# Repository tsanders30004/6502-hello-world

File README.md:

# 6502 'HELLO WORLD 6502' PCB

## INTRODUCTION
- The repo has all of the files necessary to build Ben Eater's HELLO WORLD 8-bit computer on a PCB.
- When I started my 6502 learning journey two years ago, it was so I could learn more about 6502 assembly language.
- I had little interest in hardware at the time.
- While I was doing my research, I stumbled on Ben Eater's '8-bit computer on a breadboard' YouTube series and decided to build my own computer.
- I quickly grew frustrated with breadboards so I decided to build a PCB instead.
- After many YouTube vidoes and a failed prototype, I was able to get a working PCB.
- The files in this repo are the result.

## EDA SOFTWARE
The schematics and PCB were designed with KiCad version 6.

## SCHEMATICS
- KiCad and PDF schematics are included.

### Bus vs. Labels

- When I drew the schematics, I could not figure out how to draw a bus.
- Instead, I used lables for the address and data pins, and a few other things.

## INPUTS
### Power
+5 and GND are connected to the circuit via the header pins in the upper-right corner of the PCB.

The PWR LED will illuminate when the PCB has power.

### Clock
You will need an external clock.

The clock signal should be connected to the CLK input pin in the upper-right corner of the PCB.

The CLK LED will illuminate when the circuit has a clock signal.

## OUTPUTS 
### Address and Data Pins
Output pins for each of the data and address lines are arranged vertically along the right side of the PCB.

You can connect these pins to an Arduino, oscilloscope, logic analyzer, etc. if you wish.

Leave them unconnected if you don't want to use them.

### LED's
There are LED's for each of the address and data lines along the bottom.  The LED's will illuminate when a program is running.

## IRQB and RESETB
Note the IRQB and RESETB switches directly above the 65C02 socket. 

When I drew the schematic, I was not certain how to wire the IRQB and RESETB signals using a button.  So I decided to use a slider switch instead; that way, I could connect/disconnect these signals however I wanted.

###  Resetting the Circuit
IMPORTANT:  To reset the cicuit, do the following:

1. Put the IRQB and RESETB slider switches in the UP position.
1. Put the IRQB slider switch in the DOWN position.
1. Put the RESETB slider switch in the DOWN position.

## FILES
|Filename|Description|
|-|-|
|6502_hello_world.kicad_pro|KiCad Project File|
|6502_hello_world.kicad_sch|KiCad Schematic File|
|6502_hello_world.kicad_pcb|KiCad PCB File|
|gerber_files.zip|Gerber Files|
|hello.s|Hello World Source Code|
|hello.out|Hello World Binary File|
|pcb_3d_model.png|Screen Shot of 3D Model|
|schematic.pdf|Schematics|

## CLOSING COMMENTS
- I am a hobbyist.  This is my first attempt at designing a PCB.
- When I started this project, I knew the basics of digital hardware.  But I knew nothing about PCB design.
- I learned how to solder and how to use KiCad via YouTube videos.
- PBCWay used the included gerber files to build the PCB.  They are probably suitable for other PCB manufacturers.
- If not, you can export you own gerber files with KiCad.

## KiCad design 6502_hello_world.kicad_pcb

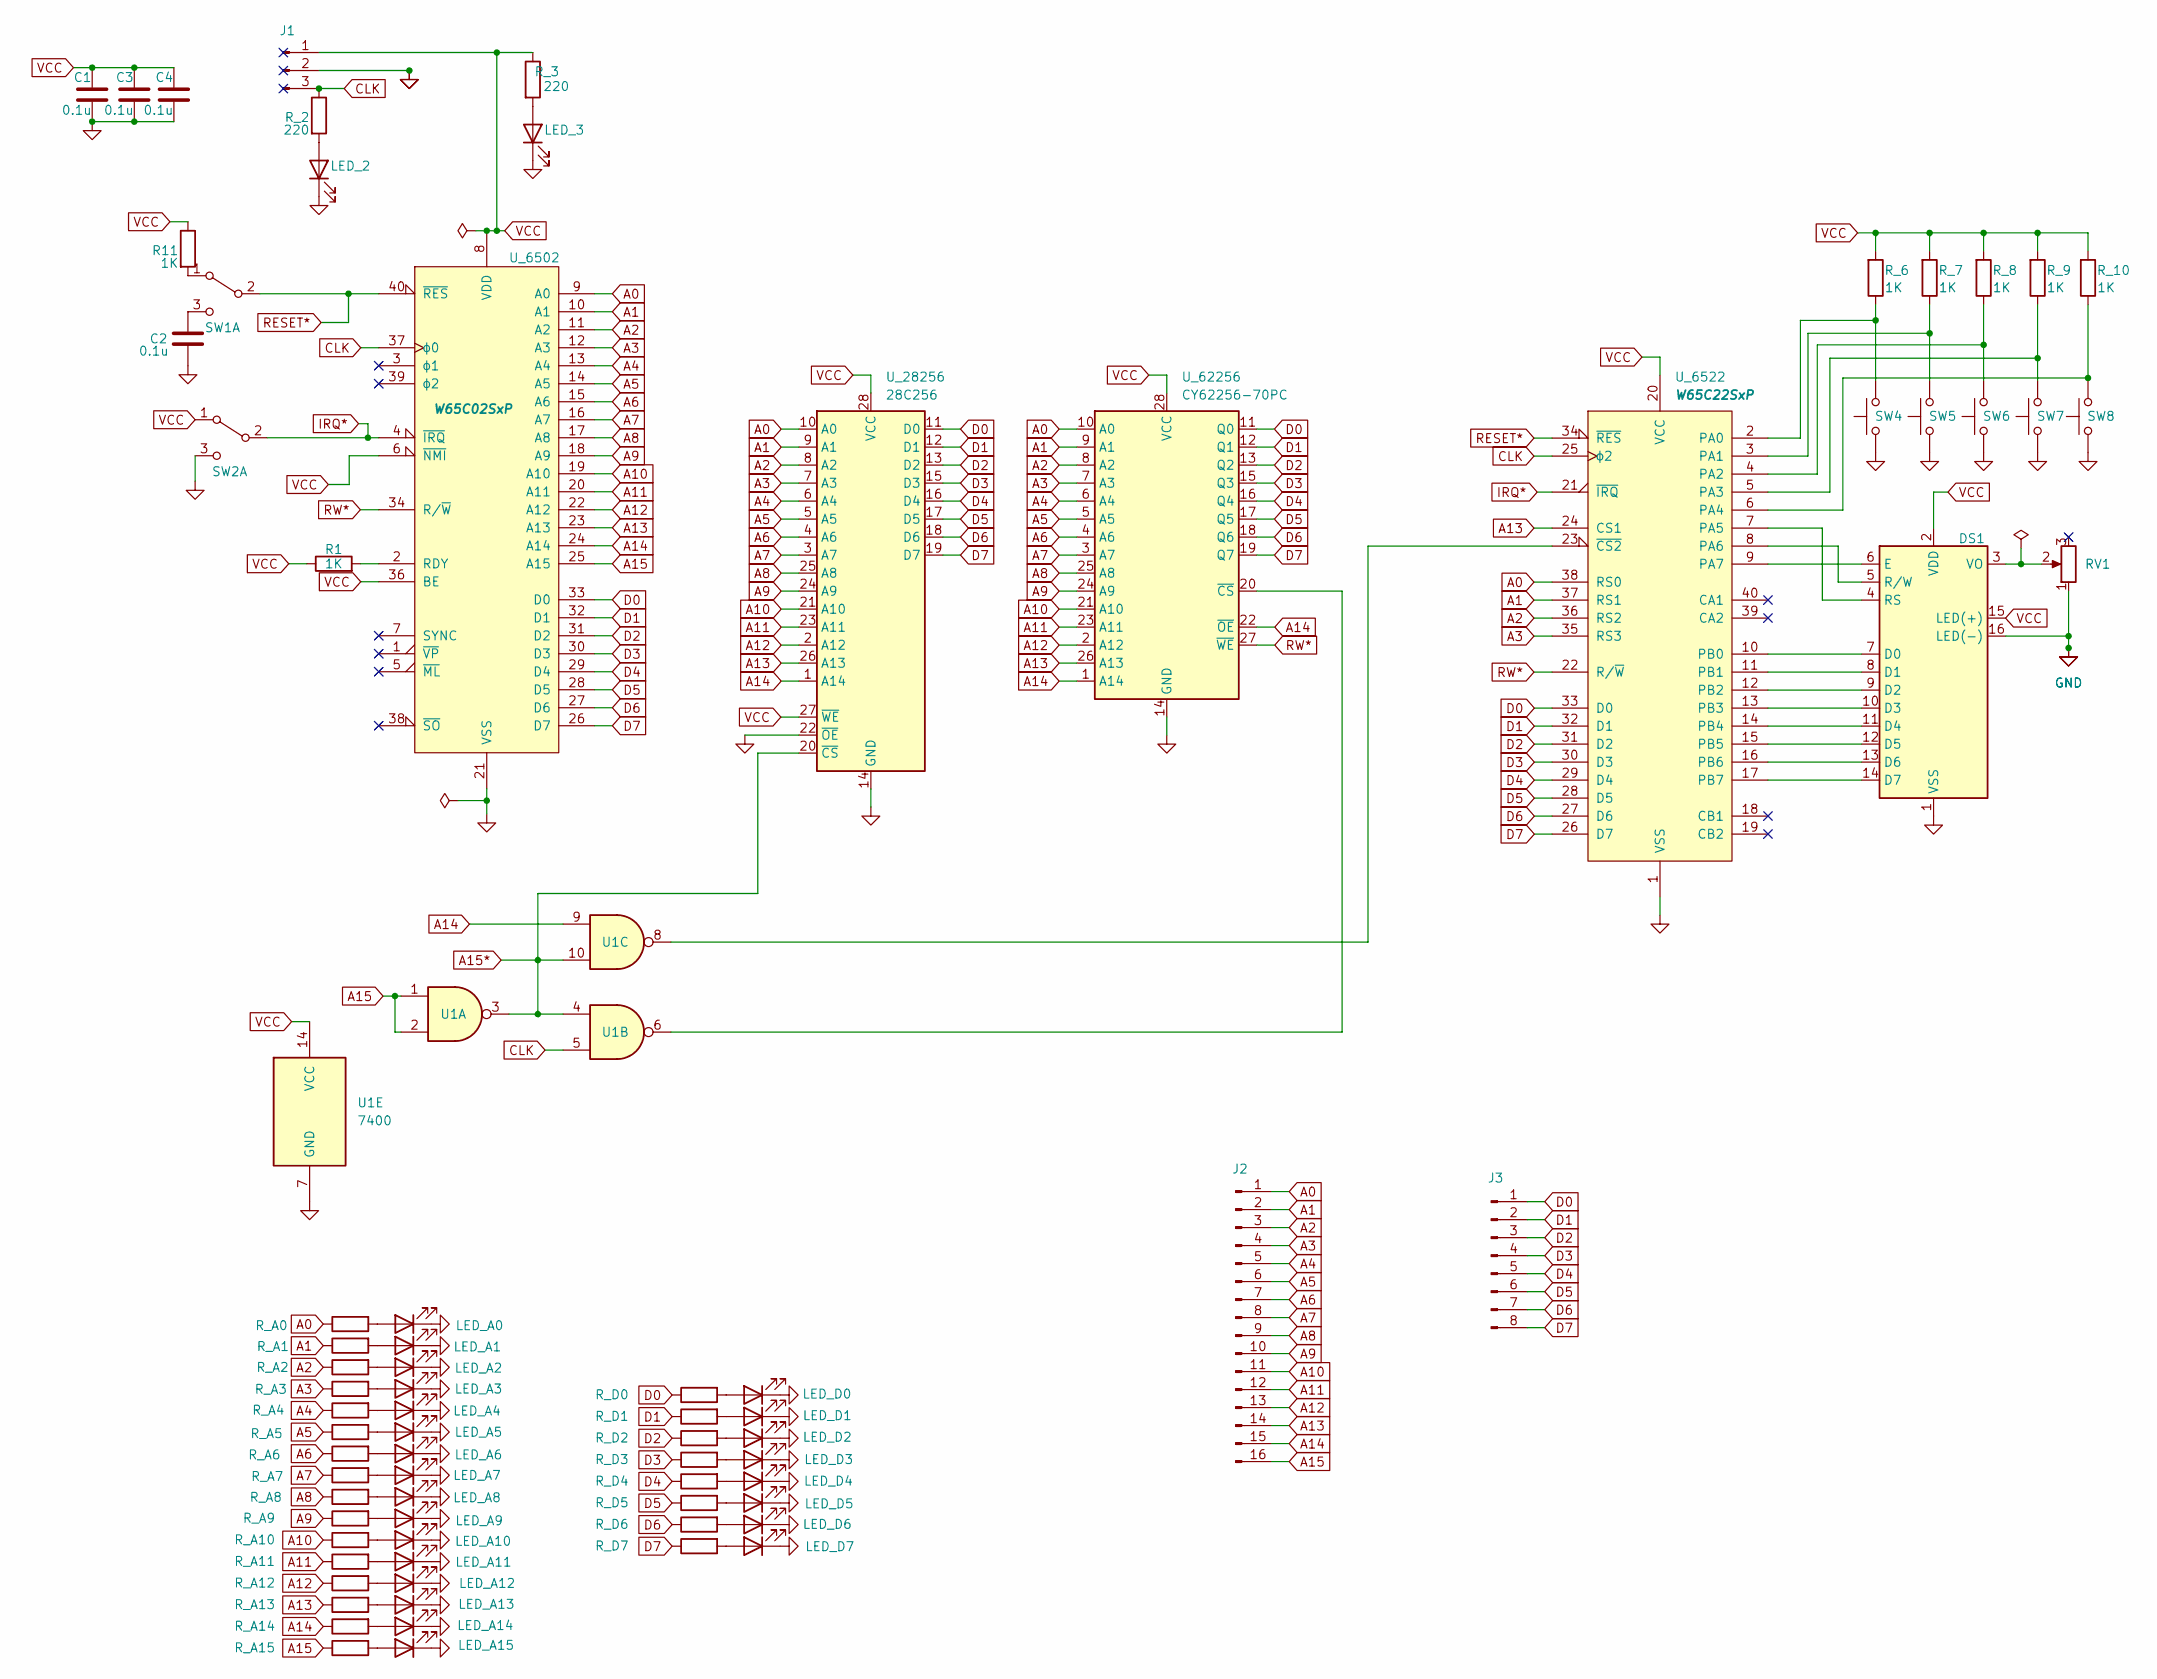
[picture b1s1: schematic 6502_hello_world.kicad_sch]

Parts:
C1, C2, C3, C4: 0.1u; C_Disc_D5.0mm_W2.5mm_P5.00mm
DS1: WC1602A
J1: Conn_01x03_Male; PinHeader_1x03_P2.54mm_Horizontal
J2: Conn_01x16_Male; PinHeader_1x16_P2.54mm_Horizontal
J3: Conn_01x08_Male; PinHeader_1x08_P2.54mm_Horizontal
LED_2, LED_3: LED; LED_D5.0mm
LED_A0, LED_A1, LED_A2, LED_A3, LED_A4, LED_A5, LED_A6, LED_A7, LED_A8, LED_A9, LED_A10, LED_A11, LED_A12, LED_A13, LED_A14, LED_A15: LED; LED_D5.0mm
LED_D0, LED_D1, LED_D2, LED_D3, LED_D4, LED_D5, LED_D6, LED_D7: LED; LED_D5.0mm
R1, R11: 1K; R_Axial_DIN0207_L6.3mm_D2.5mm_P10.16mm_Horizontal
RV1: R_Potentiometer; Potentiometer_Bourns_3266Y_Vertical
R_2, R_3: 220; R_Axial_DIN0207_L6.3mm_D2.5mm_P10.16mm_Horizontal
R_6, R_7, R_8, R_9, R_10: 1K; R_Axial_DIN0207_L6.3mm_D2.5mm_P10.16mm_Horizontal
R_A0, R_A1, R_A2, R_A3, R_A4, R_A5, R_A6, R_A7, R_A8, R_A9, R_A10, R_A11, R_A12, R_A13, R_A14, R_A15: 220; R_Axial_DIN0207_L6.3mm_D2.5mm_P10.16mm_Horizontal
R_D0, R_D1, R_D2, R_D3, R_D4, R_D5, R_D6, R_D7: 220; R_Axial_DIN0207_L6.3mm_D2.5mm_P10.16mm_Horizontal
SW1, SW2: SW_DPDT_x2; SW_SPDT_2
SW4, SW5, SW6, SW7, SW8: SW_Push; SW_PUSH_6mm_H4.3mm
U1: 7400; DIP-14_W7.62mm_Socket
U_6502: W65C02SxP; DIP-40_W15.24mm_Socket
U_6522: W65C22SxP; DIP-40_W15.24mm_Socket
U_28256: 28C256; DIP-28_W15.24mm_Socket
U_62256: CY62256-70PC; DIP-28_W15.24mm_Socket

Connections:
A0: J2.1, R_A0.1, U_6502.9 (A0), U_6522.38 (RS0), U_28256.10 (A0), U_62256.10 (A0)
A1: J2.2, R_A1.1, U_6502.10 (A1), U_6522.37 (RS1), U_28256.9 (A1), U_62256.9 (A1)
A2: J2.3, R_A2.1, U_6502.11 (A2), U_6522.36 (RS2), U_28256.8 (A2), U_62256.8 (A2)
A3: J2.4, R_A3.1, U_6502.12 (A3), U_6522.35 (RS3), U_28256.7 (A3), U_62256.7 (A3)
A4: J2.5, R_A4.1, U_6502.13 (A4), U_28256.6 (A4), U_62256.6 (A4)
A5: J2.6, R_A5.1, U_6502.14 (A5), U_28256.5 (A5), U_62256.5 (A5)
A6: J2.7, R_A6.1, U_6502.15 (A6), U_28256.4 (A6), U_62256.4 (A6)
A7: J2.8, R_A7.1, U_6502.16 (A7), U_28256.3 (A7), U_62256.3 (A7)
A8: J2.9, R_A8.1, U_6502.17 (A8), U_28256.25 (A8), U_62256.25 (A8)
A9: J2.10, R_A9.1, U_6502.18 (A9), U_28256.24 (A9), U_62256.24 (A9)
A10: J2.11, R_A10.1, U_6502.19 (A10), U_28256.21 (A10), U_62256.21 (A10)
A11: J2.12, R_A11.1, U_6502.20 (A11), U_28256.23 (A11), U_62256.23 (A11)
A12: J2.13, R_A12.1, U_6502.22 (A12), U_28256.2 (A12), U_62256.2 (A12)
A13: J2.14, R_A13.1, U_6502.23 (A13), U_6522.24 (CS1), U_28256.26 (A13), U_62256.26 (A13)
A14: J2.15, R_A14.1, U1.9, U_6502.24 (A14), U_28256.1 (A14), U_62256.1 (A14), U_62256.22 (~OE)
A15: J2.16, R_A15.1, U1.1, U1.2, U_6502.25 (A15)
A15*: U1.3, U1.4, U1.10, U_28256.20 (~CS)
CLK: J1.3, R_2.1, U1.5, U_6502.37 (ϕ0), U_6522.25 (ϕ2)
D0: J3.1, R_D0.1, U_6502.33 (D0), U_6522.33 (D0), U_28256.11 (D0), U_62256.11 (Q0)
D1: J3.2, R_D1.1, U_6502.32 (D1), U_6522.32 (D1), U_28256.12 (D1), U_62256.12 (Q1)
D2: J3.3, R_D2.1, U_6502.31 (D2), U_6522.31 (D2), U_28256.13 (D2), U_62256.13 (Q2)
D3: J3.4, R_D3.1, U_6502.30 (D3), U_6522.30 (D3), U_28256.15 (D3), U_62256.15 (Q3)
D4: J3.5, R_D4.1, U_6502.29 (D4), U_6522.29 (D4), U_28256.16 (D4), U_62256.16 (Q4)
D5: J3.6, R_D5.1, U_6502.28 (D5), U_6522.28 (D5), U_28256.17 (D5), U_62256.17 (Q5)
D6: J3.7, R_D6.1, U_6502.27 (D6), U_6522.27 (D6), U_28256.18 (D6), U_62256.18 (Q6)
D7: J3.8, R_D7.1, U_6502.26 (D7), U_6522.26 (D7), U_28256.19 (D7), U_62256.19 (Q7)
GND: C1.2, C2.2, C3.2, C4.2, DS1.1 (VSS), DS1.16 (LED(-)), J1.2, LED_2.1 (K), LED_3.1 (K), LED_A0.1 (K), LED_A1.1 (K), LED_A2.1 (K), LED_A3.1 (K), LED_A4.1 (K), LED_A5.1 (K), LED_A6.1 (K), LED_A7.1 (K), LED_A8.1 (K), LED_A9.1 (K), LED_A10.1 (K), LED_A11.1 (K), LED_A12.1 (K), LED_A13.1 (K), LED_A14.1 (K), LED_A15.1 (K), LED_D0.1 (K), LED_D1.1 (K), LED_D2.1 (K), LED_D3.1 (K), LED_D4.1 (K), LED_D5.1 (K), LED_D6.1 (K), LED_D7.1 (K), RV1.1, SW2.3 (C), SW4.2, SW5.2, SW6.2, SW7.2, SW8.2, U1.7 (GND), U_6502.21 (VSS), U_6522.1 (VSS), U_28256.14 (GND), U_28256.22 (~OE), U_62256.14 (GND)
IRQ*: SW2.2 (B), U_6502.4 (~IRQ), U_6522.21 (~IRQ)
unnamed: C2.1, SW1.3 (C)
unnamed: DS1.3 (VO), RV1.2
unnamed: DS1.4 (RS), U_6522.7 (PA5)
unnamed: DS1.5 (R/W), U_6522.8 (PA6)
unnamed: DS1.6 (E), U_6522.9 (PA7)
unnamed: DS1.7 (D0), U_6522.10 (PB0)
unnamed: DS1.8 (D1), U_6522.11 (PB1)
unnamed: DS1.9 (D2), U_6522.12 (PB2)
unnamed: DS1.10 (D3), U_6522.13 (PB3)
unnamed: DS1.11 (D4), U_6522.14 (PB4)
unnamed: DS1.12 (D5), U_6522.15 (PB5)
unnamed: DS1.13 (D6), U_6522.16 (PB6)
unnamed: DS1.14 (D7), U_6522.17 (PB7)
unnamed: LED_2.2 (A), R_2.2
unnamed: LED_3.2 (A), R_3.2
unnamed: LED_A0.2 (A), R_A0.2
unnamed: LED_A1.2 (A), R_A1.2
unnamed: LED_A2.2 (A), R_A2.2
unnamed: LED_A3.2 (A), R_A3.2
unnamed: LED_A4.2 (A), R_A4.2
unnamed: LED_A5.2 (A), R_A5.2
unnamed: LED_A6.2 (A), R_A6.2
unnamed: LED_A7.2 (A), R_A7.2
unnamed: LED_A8.2 (A), R_A8.2
unnamed: LED_A9.2 (A), R_A9.2
unnamed: LED_A10.2 (A), R_A10.2
unnamed: LED_A11.2 (A), R_A11.2
unnamed: LED_A12.2 (A), R_A12.2
unnamed: LED_A13.2 (A), R_A13.2
unnamed: LED_A14.2 (A), R_A14.2
unnamed: LED_A15.2 (A), R_A15.2
unnamed: LED_D0.2 (A), R_D0.2
unnamed: LED_D1.2 (A), R_D1.2
unnamed: LED_D2.2 (A), R_D2.2
unnamed: LED_D3.2 (A), R_D3.2
unnamed: LED_D4.2 (A), R_D4.2
unnamed: LED_D5.2 (A), R_D5.2
unnamed: LED_D6.2 (A), R_D6.2
unnamed: LED_D7.2 (A), R_D7.2
unnamed: R1.2, U_6502.2 (RDY)
unnamed: R11.2, SW1.1 (A)
unnamed: R_6.1, SW4.1, U_6522.2 (PA0)
unnamed: R_7.1, SW5.1, U_6522.3 (PA1)
unnamed: R_8.1, SW6.1, U_6522.4 (PA2)
unnamed: R_9.1, SW7.1, U_6522.5 (PA3)
unnamed: R_10.1, SW8.1, U_6522.6 (PA4)
unnamed: U1.6, U_62256.20 (~CS)
unnamed: U1.8, U_6522.23 (~CS2)
RESET*: SW1.2 (B), U_6502.40 (~RES), U_6522.34 (~RES)
RW*: U_6502.34 (R/~W), U_6522.22 (R/~W), U_62256.27 (~WE)
VCC: C1.1, C3.1, C4.1, DS1.2 (VDD), DS1.15 (LED(+)), J1.1, R1.1, R11.1, R_3.1, R_6.2, R_7.2, R_8.2, R_9.2, R_10.2, SW2.1 (A), U1.14 (VCC), U_6502.6 (~NMI), U_6502.8 (VDD), U_6502.36 (BE), U_6522.20 (VCC), U_28256.27 (~WE), U_28256.28 (VCC), U_62256.28 (VCC)

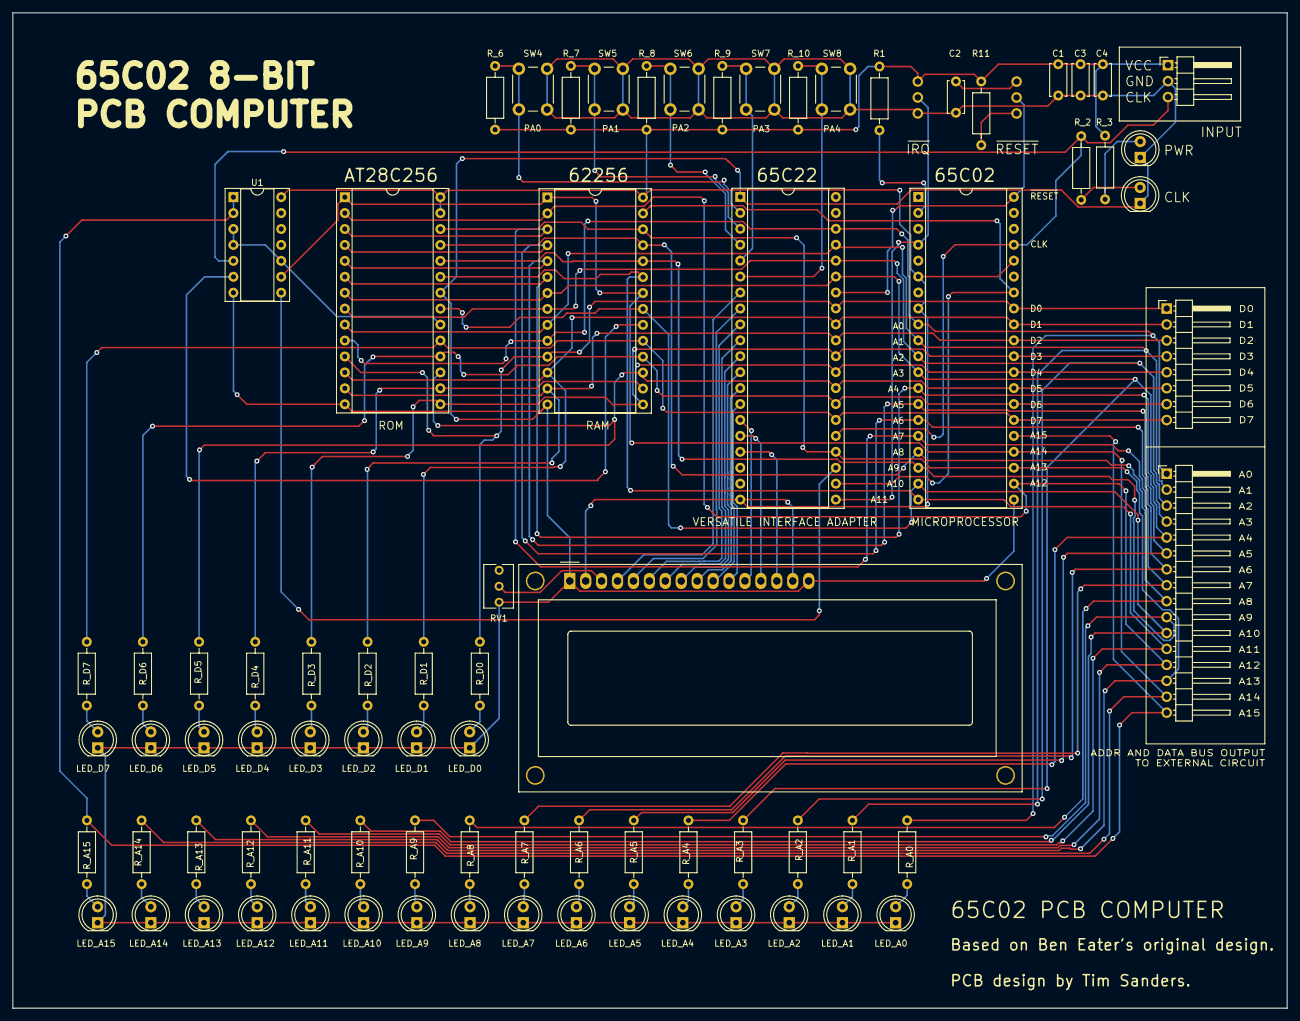
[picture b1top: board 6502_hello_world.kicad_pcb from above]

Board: 2 copper layers, 203.2 x 158.7 mm, 80 parts (0 on the bottom side), 79 nets.

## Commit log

2024-08-24 First commit.
2024-08-24 1. New Files A. 6502_hello_world.kicad_pcb B. 6502_hello_world.kicad_pro C. 6502_hello_world.kicad_sch D. README.md E. gerber_files.zip F. hello.out G. hello.s H. hello_world.png I. pcb_3d_model.png 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
